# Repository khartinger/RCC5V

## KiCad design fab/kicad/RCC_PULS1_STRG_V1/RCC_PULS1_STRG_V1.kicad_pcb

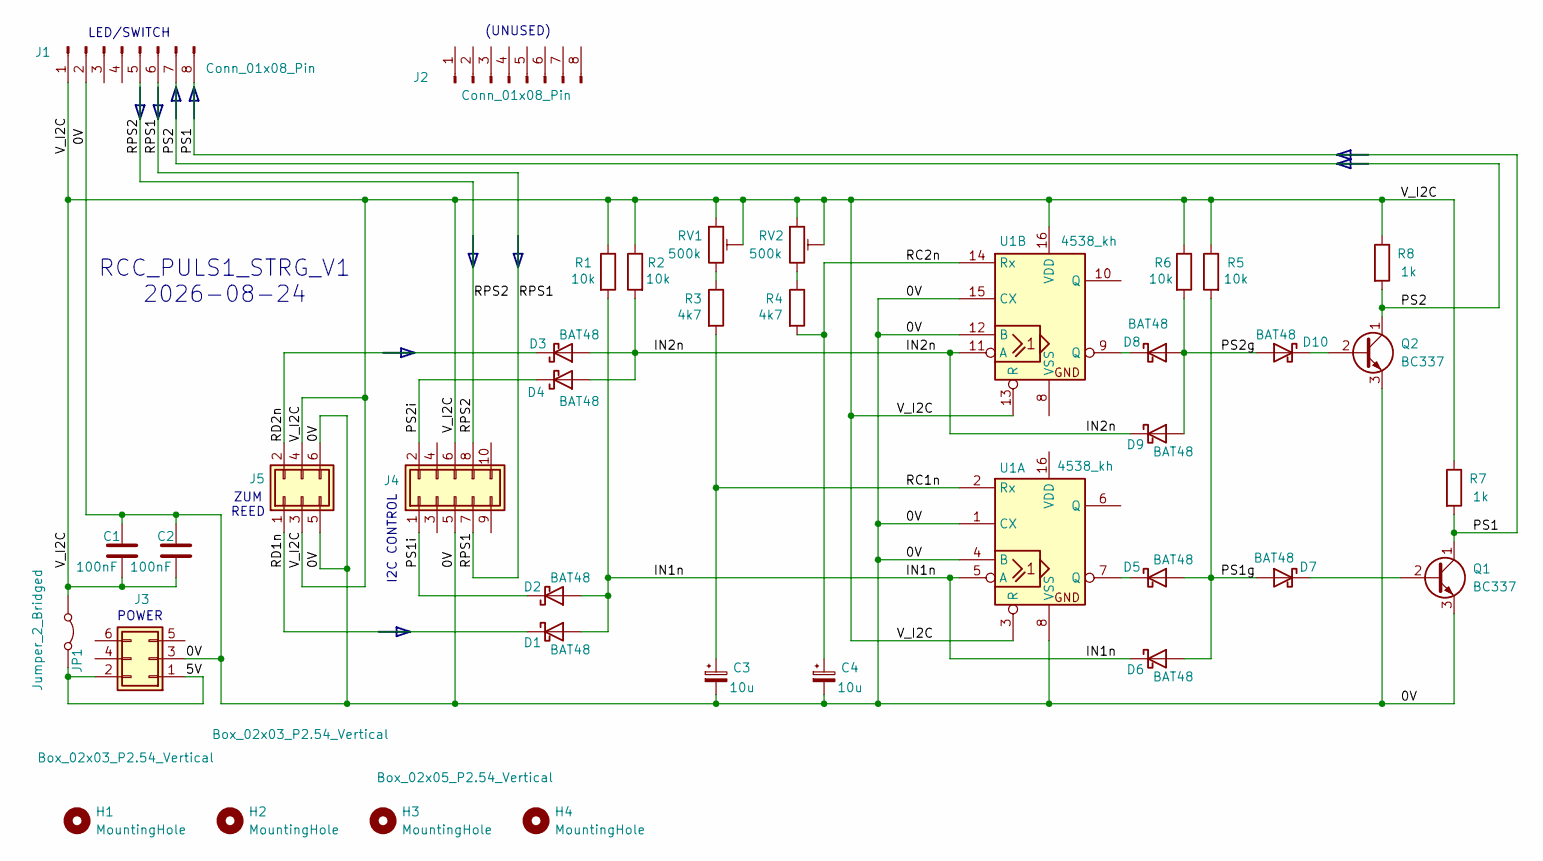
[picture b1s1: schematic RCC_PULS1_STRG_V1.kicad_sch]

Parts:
C1, C2: 100nF; C_Rect_L7.0mm_W2.0mm_P5.00mm_kh
C3, C4: 10u; ELKO_L4.32mm_D3.81mm_P2.54mm_kh
D1, D2, D3: BAT48; D_DO-35_P2.0mm_Vertical_AnodeUp_kh
D4, D5, D6, D7, D8, D9, D10: BAT48; D_DO-35_SOD27_P2.54mm_Vertical_AnodeUp_kh
H1, H2, H3, H4: MountingHole; MountingHole_2.2mm_M2_Pad_TopBottom_kh
J1, J2: Conn_01x08_Pin; PinSocket_1x08_P2.54mm_Vertical_kh
J3, J5: Box_02x03_P2.54_Vertical; Box_02x03_P2.54mm_Vertical_kh
J4: Box_02x05_P2.54_Vertical; Box_02x05_P2.54mm_Vertical_kh
JP1: Jumper_2_Bridged; SolderJumper-2_P1.3mm_Bridged_Pad1.0x1.5mm
Q1, Q2: BC337; TO-92_Inline_Wide_custom
R1, R5: 10k; R_Axial_DIN0204_L3.6mm_D1.6mm_P2.54mm_Vertical
R2, R6: 10k; R_Axial_DIN0204_L3.6mm_D1.6mm_P2.54mm_Vertical_kh
R3: 4k7; R_Axial_DIN0204_L3.6mm_D1.6mm_P2.54mm_Vertical
R4: 4k7; R_Axial_DIN0204_L3.6mm_D1.6mm_P3.81mm_Vertical_kh
R7, R8: 1k; R_Axial_DIN0204_L3.6mm_D1.6mm_P2.54mm_Vertical_kh
RV1, RV2: 500k; Trim_RM-063_Horizontal_kh
U1: 4538_kh; DIP-16_W7.62mm_kh

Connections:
/0V: C1.1, C2.1, C3.2, C4.2, J1.2, J3.3, J4.5, J5.5, J5.6, Q1.3 (E), Q2.3 (E), U1.1 (CX), U1.4 (B), U1.8 (VSS), U1.12 (B), U1.15 (CX)
/5V: J3.1, J3.2, JP1.2 (B)
/IN1n: D1.2 (A), D2.2 (A), D6.1 (K), R1.2, U1.5 (A)
/IN2n: D3.2 (A), D4.2 (A), D9.1 (K), R2.2, U1.11 (A)
/PS1: J1.8, Q1.1 (C), R7.2
/PS1g: D5.2 (A), D6.2 (A), D7.2 (A), R5.2
/PS1i: D2.1 (K), J4.1
/PS2: J1.7, Q2.1 (C), R8.2
/PS2g: D8.2 (A), D9.2 (A), D10.2 (A), R6.2
/PS2i: D4.1 (K), J4.2
/RC1n: C3.1, R3.2, U1.2 (Rx)
/RC2n: C4.1, R4.2, U1.14 (Rx)
/RD1n: D1.1 (K), J5.1
/RD2n: D3.1 (K), J5.2
/RPS1: J1.6, J4.7
/RPS2: J1.5, J4.8
/V_I2C: C1.2, C2.2, J1.1, J4.6, J5.3, J5.4, JP1.1 (A), R1.1, R2.1, R5.1, R6.1, R7.1, R8.1, RV1.1, RV1.2, RV2.1, RV2.2, U1.3 (R), U1.13 (R), U1.16 (VDD)
unnamed: D5.1 (K), U1.7 (Q)
unnamed: D7.1 (K), Q1.2 (B)
unnamed: D8.1 (K), U1.9 (Q)
unnamed: D10.1 (K), Q2.2 (B)
unnamed: R3.1, RV1.3
unnamed: R4.1, RV2.3

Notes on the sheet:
ZUM REED
RCC_PULS1_STRG_V1 2026-08-24
I2C CONTROL
POWER
(UNUSED)
LED/SWITCH

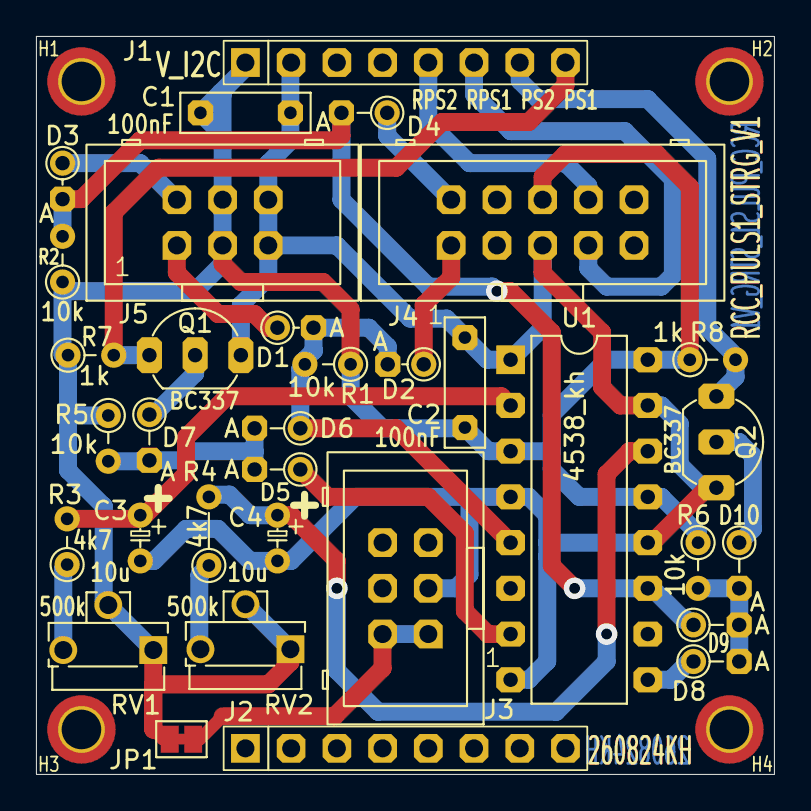
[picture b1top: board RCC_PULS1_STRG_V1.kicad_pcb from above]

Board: 2 copper layers, 41.0 x 41.0 mm, 37 parts (0 on the bottom side), 23 nets.

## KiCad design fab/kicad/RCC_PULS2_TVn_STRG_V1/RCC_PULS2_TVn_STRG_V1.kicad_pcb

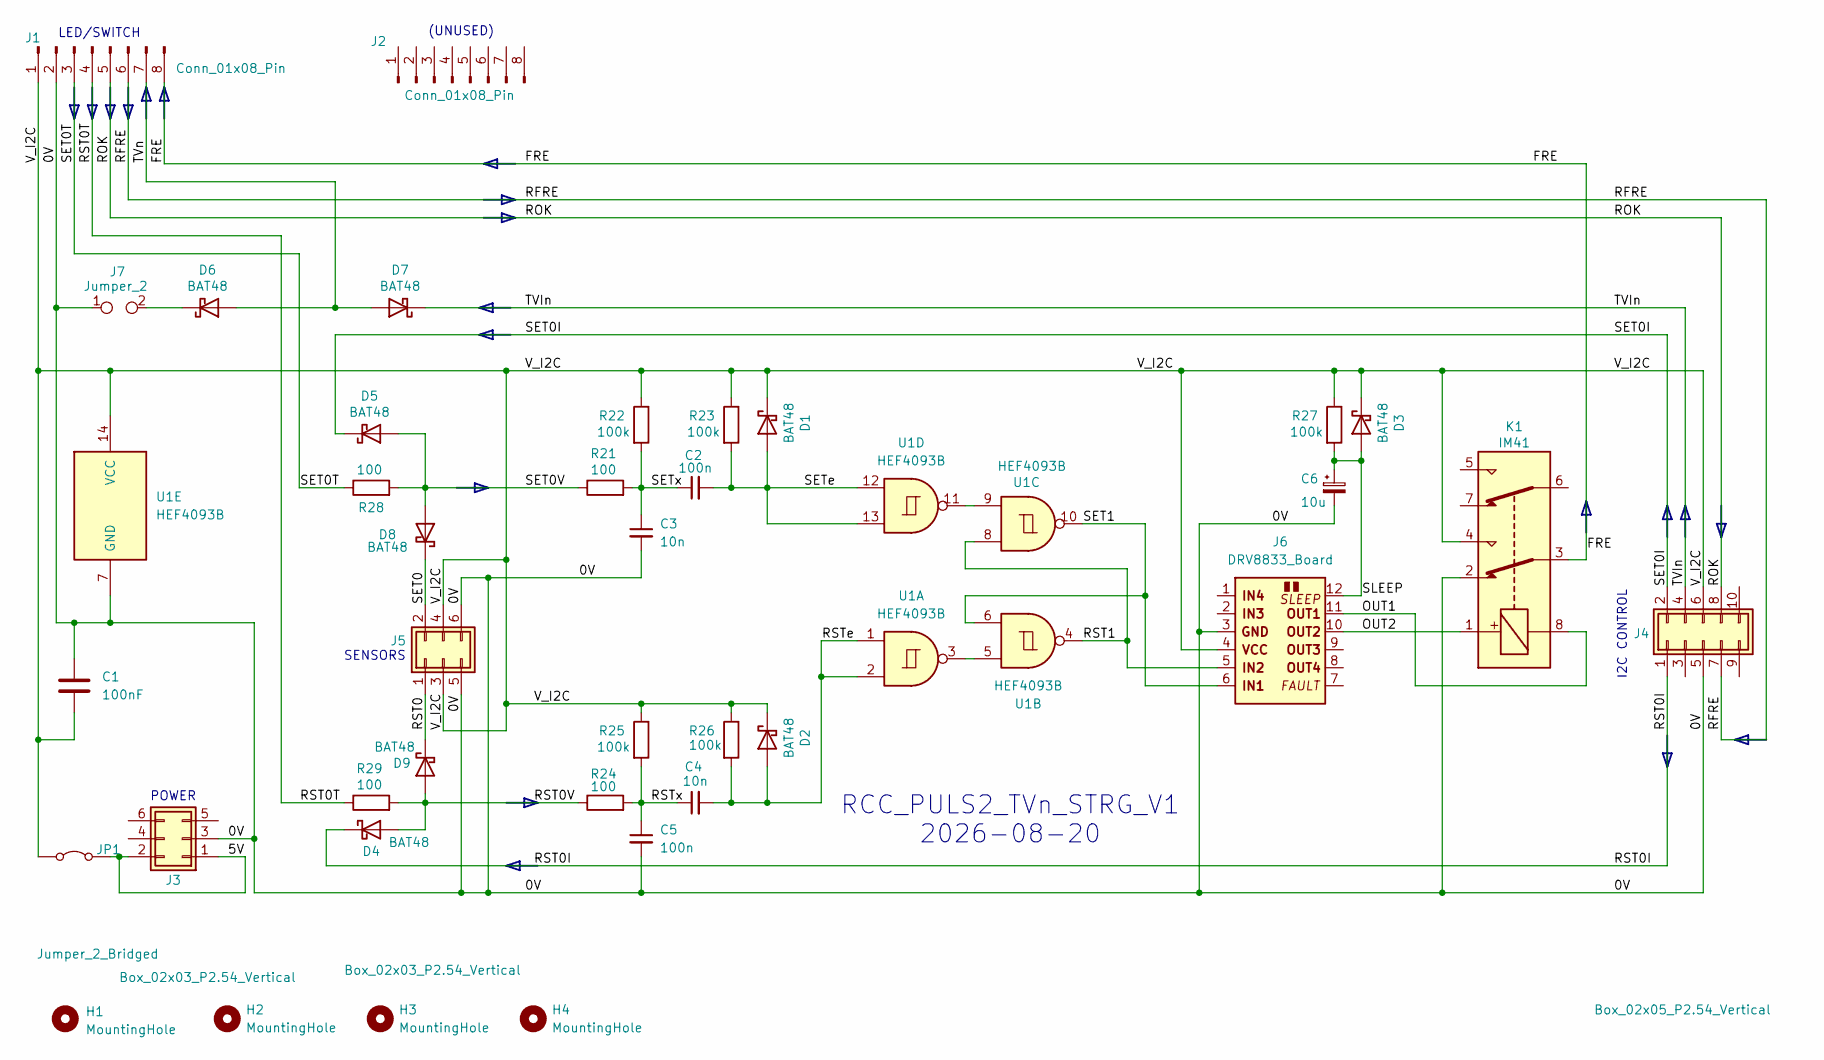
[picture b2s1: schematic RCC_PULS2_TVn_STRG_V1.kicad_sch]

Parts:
C1: 100nF; C_L4mm_D3mm_P2.54mm_kh
C2, C5: 100n; C_L4mm_D3mm_P2.54mm_kh
C3, C4: 10n; C_L4mm_D3mm_P2.54mm_kh
C6: 10u; ELKO_L7.88mm_D4.57mm_P2.54mm_kh
D1, D2, D4: BAT48; D_DO-35_P1.778mm_Vertical_AnodeUp_kh
D3, D6: BAT48; D_DO-35_SOD27_P5.08mm_Horizontal_kh
D5, D8, D9: BAT48; D_DO-35_P2.0mm_Vertical_AnodeUp_kh
D7: BAT48; D_DO-35_SOD27_P2.54mm_Vertical_AnodeUp
H1, H2, H3, H4: MountingHole; MountingHole_2.2mm_M2_Pad_TopBottom_kh
J1, J2: Conn_01x08_Pin; PinSocket_1x08_P2.54mm_Vertical_Back_kh
J3, J5: Box_02x03_P2.54_Vertical; Box_02x03_P2.54mm_Vertical_kh
J4: Box_02x05_P2.54_Vertical; Box_02x05_P2.54mm_Vertical_kh
J6: DRV8833_Board
J7: Jumper_2; PinSocket_1x02_P2.54mm_Vertical_kh
JP1: Jumper_2_Bridged; SolderJumper-2_P1.3mm_Bridged_Pad1.0x1.5mm
K1: IM41; Relay_DPDT_AXICOM_IMSeries_Pitch5.08mm_rect_Pins
R21, R24: 100; R_Axial_P1.778mm_Vertical_kh
R22, R23, R25, R26: 100k; R_Axial_P1.778mm_Vertical_kh
R27: 100k; R_Axial_DIN0204_L3.6mm_D1.6mm_P7.62mm_Horizontal
R28, R29: 100; R_Axial_DIN0204_L3.6mm_D1.6mm_P2.54mm_Vertical_kh
U1: HEF4093B; DIP-14_W7.62mm_Socket_kh

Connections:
/0V: C1.1, C3.2, C5.2, C6.2, J1.2, J3.3, J4.5, J5.5, J5.6, J6.3 (GND), J7.1, K1.2, U1.7 (GND)
/5V: J3.1, J3.2, JP1.2 (B)
/FRE: J1.8, K1.3
/OUT1: J6.11 (OUT1), K1.8
/OUT2: J6.10 (OUT2), K1.1
/RFRE: J1.6, J4.7
/ROK: J1.5, J4.8
/RST0: D9.1 (K), J5.1
/RST0I: D4.1 (K), J4.1
/RST0T: J1.4, R29.1
/RST0V: D4.2 (A), D9.2 (A), R24.1, R29.2
/RST1: J6.5 (IN2), U1.4, U1.8
/RSTe: C4.2, D2.2 (A), R26.2, U1.1, U1.2
/RSTx: C4.1, C5.1, R24.2, R25.2
/SET0: D8.1 (K), J5.2
/SET0I: D5.1 (K), J4.2
/SET0T: J1.3, R28.1
/SET0V: D5.2 (A), D8.2 (A), R21.1, R28.2
/SET1: J6.6 (IN1), U1.6, U1.10
/SETe: C2.2, D1.2 (A), R23.2, U1.12, U1.13
/SETx: C2.1, C3.1, R21.2, R22.2
/SLEEP: C6.1, D3.2 (A), J6.12 (SLEEP), R27.2
/TVIn: D7.1 (K), J4.4
/TVn: D6.2 (A), D7.2 (A), J1.7
/V_I2C: C1.2, D1.1 (K), D2.1 (K), D3.1 (K), J1.1, J4.6, J5.3, J5.4, J6.4 (VCC), JP1.1 (A), K1.4, R22.1, R23.1, R25.1, R26.1, R27.1, U1.14 (VCC)
unnamed: D6.1 (K), J7.2
unnamed: U1.3, U1.5
unnamed: U1.9, U1.11

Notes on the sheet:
SENSORS
I2C CONTROL
POWER
(UNUSED)
LED/SWITCH
RCC_PULS2_TVn_STRG_V1 2026-08-20

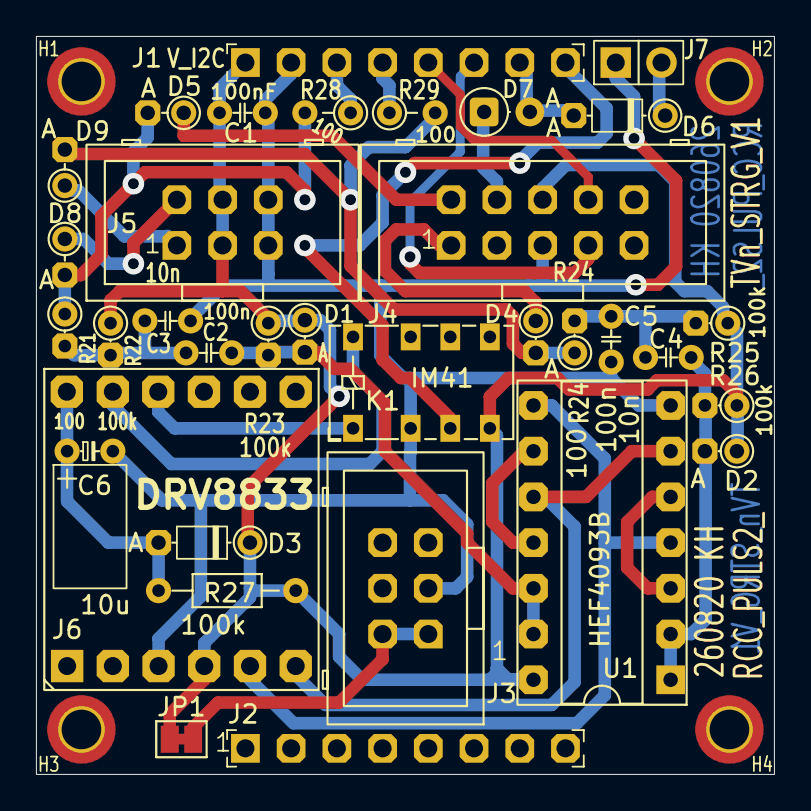
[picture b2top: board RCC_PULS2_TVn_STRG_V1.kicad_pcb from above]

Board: 2 copper layers, 41.0 x 41.0 mm, 38 parts (0 on the bottom side), 28 nets.

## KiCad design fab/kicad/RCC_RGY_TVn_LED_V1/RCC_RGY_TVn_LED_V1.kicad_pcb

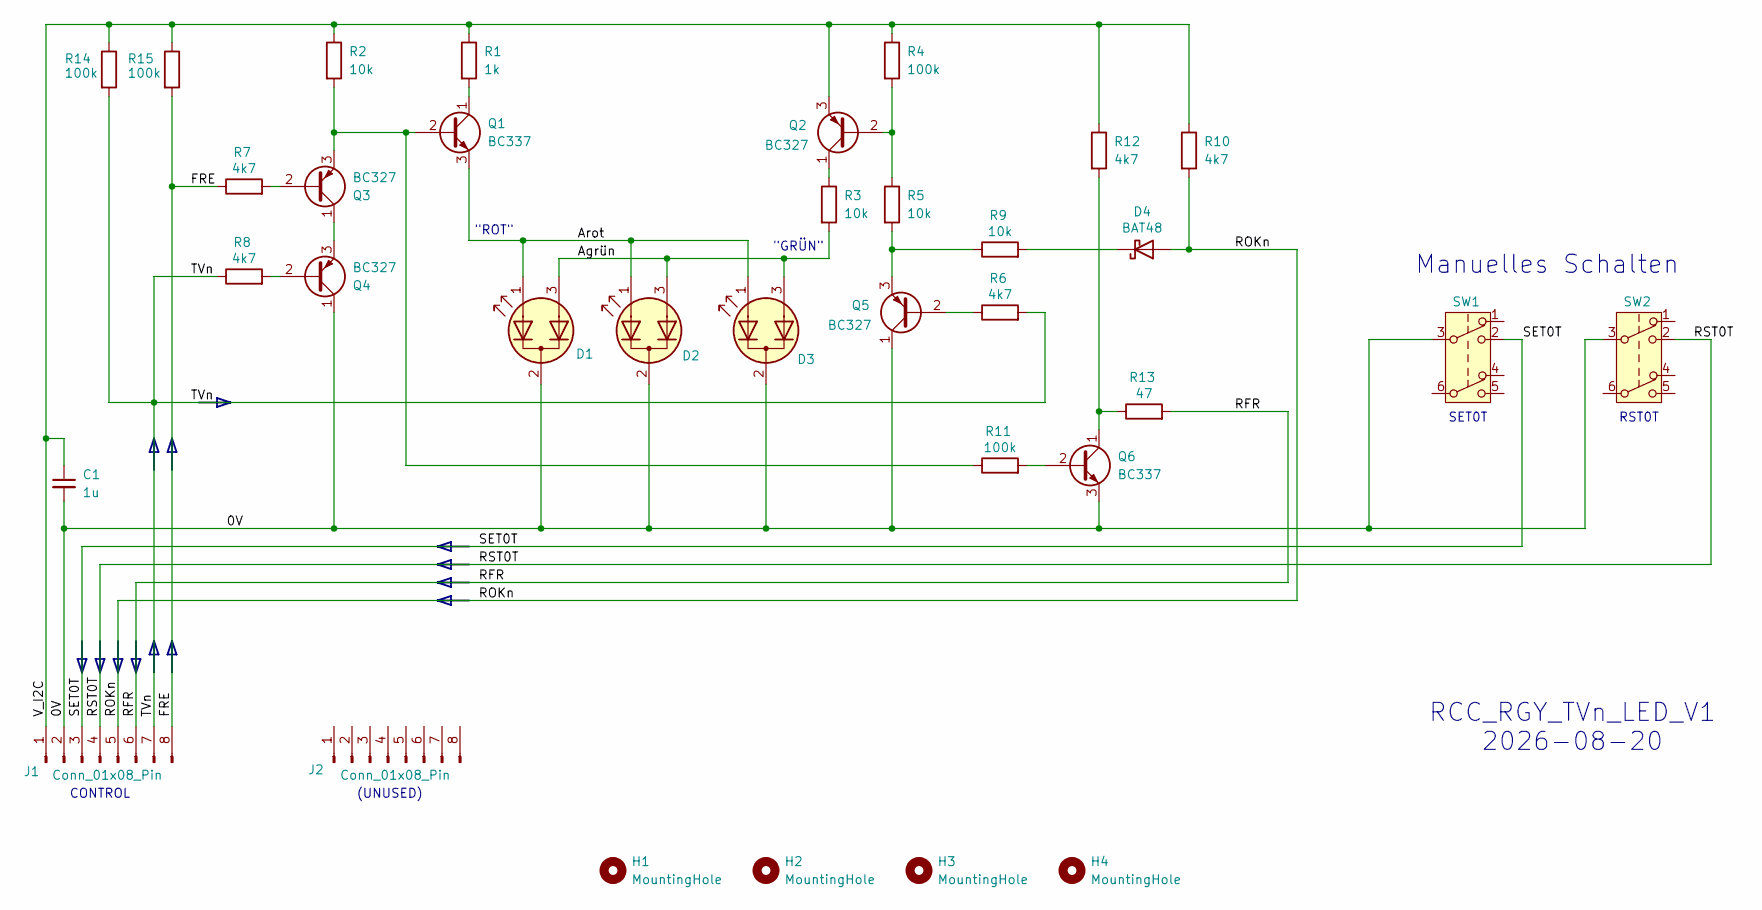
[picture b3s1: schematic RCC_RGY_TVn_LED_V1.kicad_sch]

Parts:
C1: 1u; C_L4mm_D3mm_P2.54mm_kh
D1, D2, D3: LED_Dual_AKA; LED_D5.0mm-3
D4: BAT48; D_DO-35_SOD27_P2.54mm_Vertical_AnodeUp
H1, H2, H3, H4: MountingHole; MountingHole_2.2mm_M2_Pad_TopBottom_kh
J1, J2: Conn_01x08_Pin; PinSocket_1x08_P2.54mm_Vertical_11mm_kh
Q1, Q6: BC337; TO-92_Inline_Wide_custom
Q2, Q3, Q4, Q5: BC327; TO-92_Inline_Wide_custom
R1: 1k; R_Axial_DIN0204_L3.6mm_D1.6mm_P7.62mm_Horizontal
R2, R3, R5: 10k; R_Axial_DIN0204_L3.6mm_D1.6mm_P2.54mm_Vertical
R4, R14, R15: 100k; R_Axial_DIN0204_L3.6mm_D1.6mm_P2.54mm_Vertical
R6, R8: 4k7; R_Axial_DIN0204_L3.6mm_D1.6mm_P2.54mm_Vertical_kh
R7: 4k7; R_Axial_DIN0204_L3.6mm_D1.6mm_P3.81mm_Vertical_kh
R9: 10k; R_Axial_DIN0204_L3.6mm_D1.6mm_P2.54mm_Vertical_kh
R10, R12: 4k7; R_Axial_DIN0204_L3.6mm_D1.6mm_P2.54mm_Vertical
R11: 100k; R_Axial_DIN0204_L3.6mm_D1.6mm_P7.62mm_Horizontal
R13: 47; R_Axial_DIN0204_L3.6mm_D1.6mm_P7.62mm_Horizontal
SW1, SW2: SW_Push_DPDT_8x8

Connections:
/0V: C1.2, D1.2 (K), D2.2 (K), D3.2 (K), J1.2, Q4.1 (C), Q5.1 (C), Q6.3 (E), SW1.3 (C), SW2.3 (C)
/Agrün: D1.3 (A2), D2.3 (A2), D3.3 (A2), R3.2
/Arot: D1.1 (A1), D2.1 (A1), D3.1 (A1), Q1.3 (E)
/FRE: J1.8, R7.1, R15.2
/RFR: J1.6, R13.2
/ROKn: D4.2 (A), J1.5, R10.2
/RST0T: J1.4, SW2.2 (B)
/SET0T: J1.3, SW1.2 (B)
/TVn: J1.7, R6.2, R8.1, R14.2
/V_I2C: C1.1, J1.1, Q2.3 (E), R1.1, R2.1, R4.1, R10.1, R12.1, R14.1, R15.1
unnamed: D4.1 (K), R9.2
unnamed: Q1.2 (B), Q3.3 (E), R2.2, R11.1
unnamed: Q1.1 (C), R1.2
unnamed: Q2.2 (B), R4.2, R5.1
unnamed: Q2.1 (C), R3.1
unnamed: Q3.2 (B), R7.2
unnamed: Q3.1 (C), Q4.3 (E)
unnamed: Q4.2 (B), R8.2
unnamed: Q5.2 (B), R6.1
unnamed: Q5.3 (E), R5.2, R9.1
unnamed: Q6.2 (B), R11.2
unnamed: Q6.1 (C), R12.2, R13.1

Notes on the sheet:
(UNUSED)
SET0T
Manuelles Schalten
"GRÜN"
RCC_RGY_TVn_LED_V1 2026-08-20
CONTROL
"ROT"
RST0T

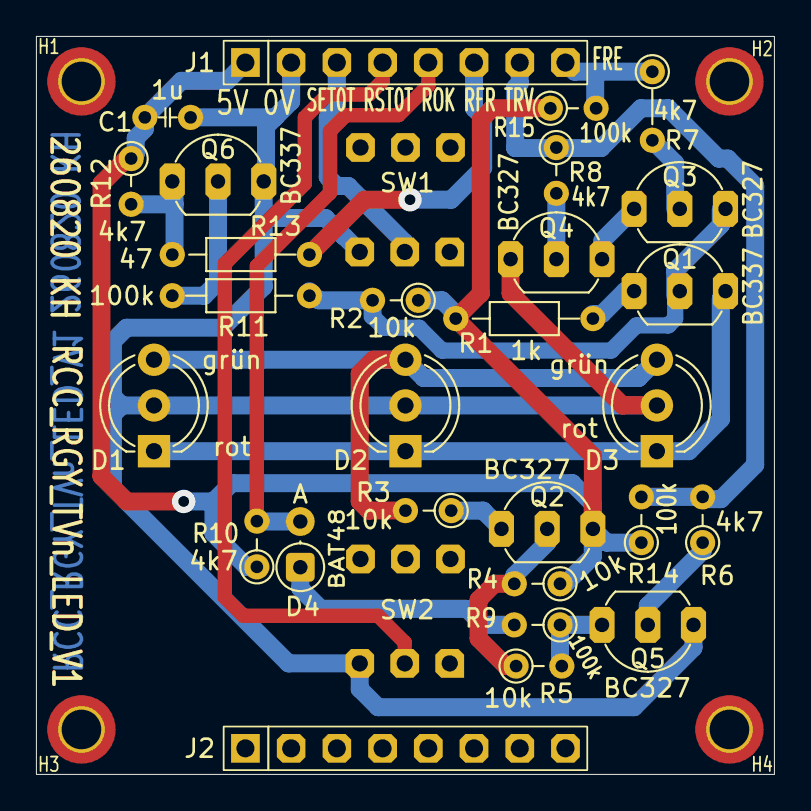
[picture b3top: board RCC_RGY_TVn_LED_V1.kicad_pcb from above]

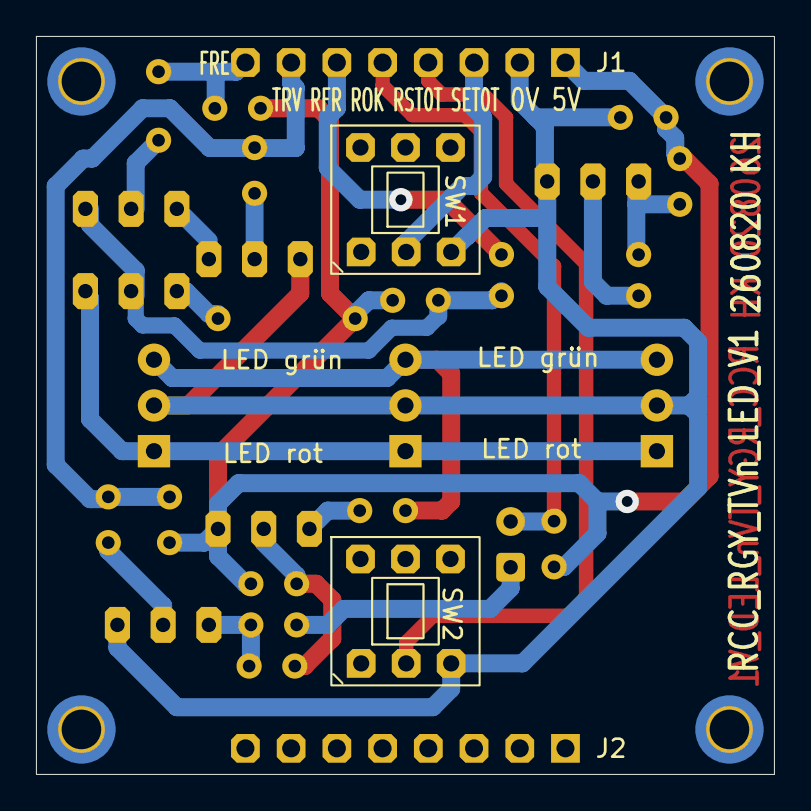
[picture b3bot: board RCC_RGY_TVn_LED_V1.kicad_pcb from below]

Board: 2 copper layers, 41.0 x 41.0 mm, 34 parts (2 on the bottom side), 22 nets.

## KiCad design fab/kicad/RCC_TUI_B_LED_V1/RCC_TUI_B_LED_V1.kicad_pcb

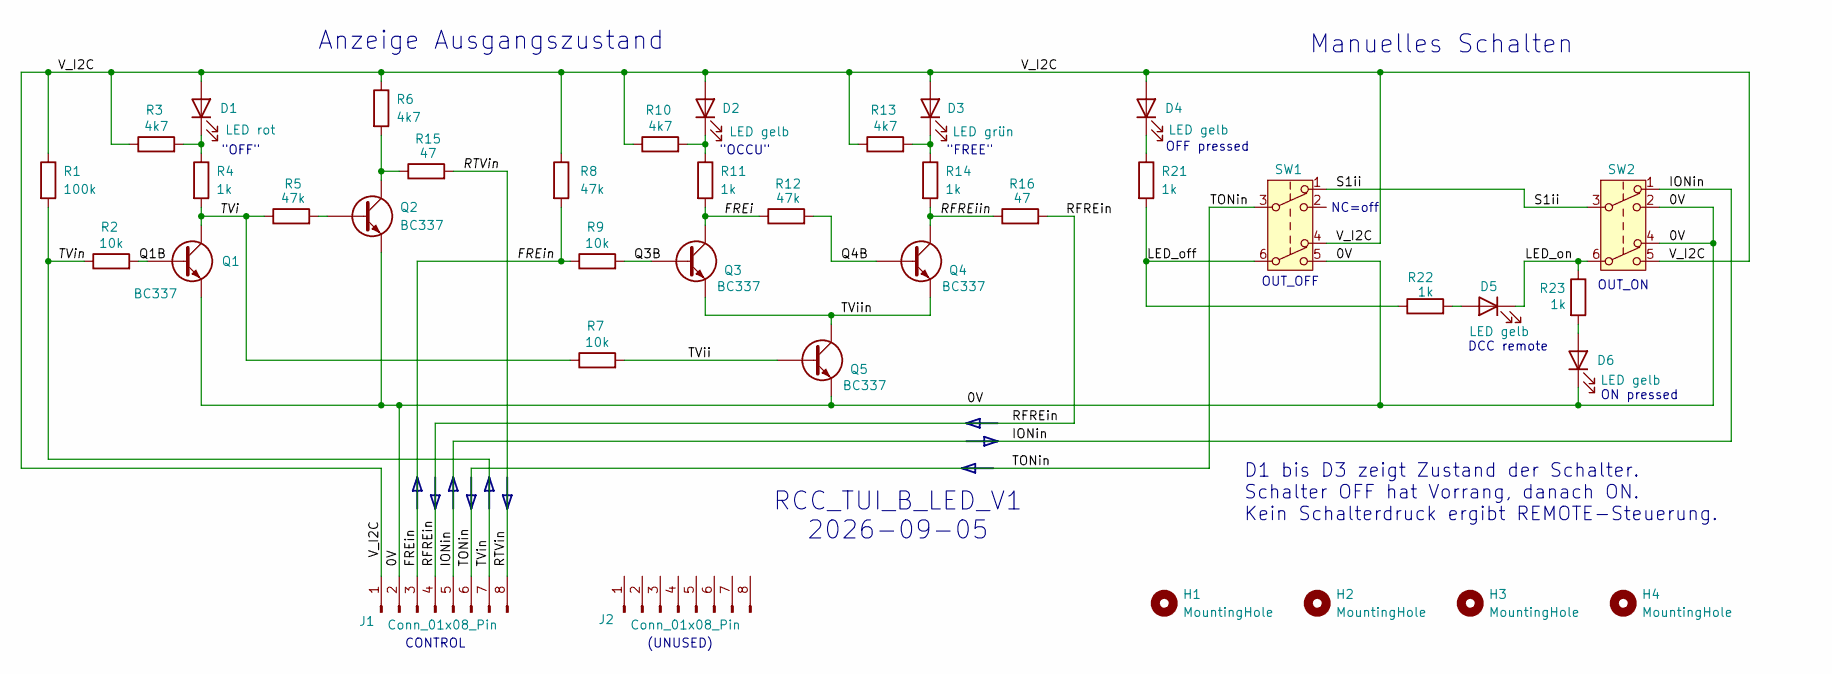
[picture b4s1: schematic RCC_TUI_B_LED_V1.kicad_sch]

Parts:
D1: LED rot; LED_D3.0mm_kh
D2, D4, D5, D6: LED gelb; LED_D3.0mm_kh
D3: LED grün; LED_D3.0mm_kh
H1, H2, H3, H4: MountingHole; MountingHole_2.2mm_M2_Pad_TopBottom_kh
J1, J2: Conn_01x08_Pin; PinSocket_1x08_P2.54mm_Vertical_11mm_kh
Q1, Q2, Q3, Q4, Q5: BC337; TO-92_Inline_Wide_custom
R1: 100k; R_Axial_DIN0204_L3.6mm_D1.6mm_P2.54mm_Vertical
R2, R7, R9: 10k; R_Axial_DIN0204_L3.6mm_D1.6mm_P2.54mm_Vertical_kh
R3, R10, R13: 4k7; R_Axial_DIN0204_L3.6mm_D1.6mm_P2.54mm_Vertical_kh
R4, R21, R22, R23: 1k; R_Axial_DIN0204_L3.6mm_D1.6mm_P2.54mm_Vertical_kh
R5, R8, R12: 47k; R_Axial_DIN0204_L3.6mm_D1.6mm_P2.54mm_Vertical_kh
R6: 4k7; R_Axial_DIN0204_L3.6mm_D1.6mm_P2.54mm_Vertical
R11, R14: 1k; R_Axial_DIN0204_L3.6mm_D1.6mm_P2.54mm_Vertical
R15: 47; R_Axial_DIN0204_L3.6mm_D1.6mm_P3.81mm_Vertical_kh
R16: 47; R_Axial_DIN0207_L6.3mm_D2.5mm_P12.7mm_Horizontal_kh
SW1, SW2: SW_Push_DPDT_8x8

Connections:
/0V: D6.1 (K), J1.2, Q1.3 (E), Q2.3 (E), Q5.3 (E), SW1.5 (B), SW2.2 (B), SW2.4 (A)
/FREi: Q3.1 (C), R11.2, R12.1
/FREin: J1.3, R8.2, R9.1
/IONin: J1.5, SW2.1 (A)
/LED_off: R21.2, R22.1, SW1.6 (C)
/LED_on: D5.1 (K), R23.1, SW2.6 (C)
/Q1B: Q1.2 (B), R2.2
/Q3B: Q3.2 (B), R9.2
/Q4B: Q4.2 (B), R12.2
/RFREiin: Q4.1 (C), R14.2, R16.1
/RFREin: J1.4, R16.2
/RTVin: J1.8, R15.2
/S1ii: SW1.1 (A), SW2.3 (C)
/TONin: J1.6, SW1.3 (C)
/TVi: Q1.1 (C), R4.2, R5.1, R7.1
/TVii: Q5.2 (B), R7.2
/TViin: Q3.3 (E), Q4.3 (E), Q5.1 (C)
/TVin: J1.7, R1.2, R2.1
/V_I2C: D1.2 (A), D2.2 (A), D3.2 (A), D4.2 (A), J1.1, R1.1, R3.1, R6.1, R8.1, R10.1, R13.1, SW1.4 (A), SW2.5 (B)
unnamed: D1.1 (K), R3.2, R4.1
unnamed: D2.1 (K), R10.2, R11.1
unnamed: D3.1 (K), R13.2, R14.1
unnamed: D4.1 (K), R21.1
unnamed: D5.2 (A), R22.2
unnamed: D6.2 (A), R23.2
unnamed: Q2.2 (B), R5.2
unnamed: Q2.1 (C), R6.2, R15.1

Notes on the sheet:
ON pressed
(UNUSED)
OUT_OFF
"OCCU"
D1 bis D3 zeigt Zustand der Schalter. Schalter OFF hat Vorrang, danach ON. Kein Schalterdruck ergibt REMOTE-Steuerung.
Manuelles Schalten
"OFF"
CONTROL
OUT_ON
OFF pressed
Anzeige Ausgangszustand
"FREE"
RCC_TUI_B_LED_V1 2026-09-05
DCC remote
NC=off

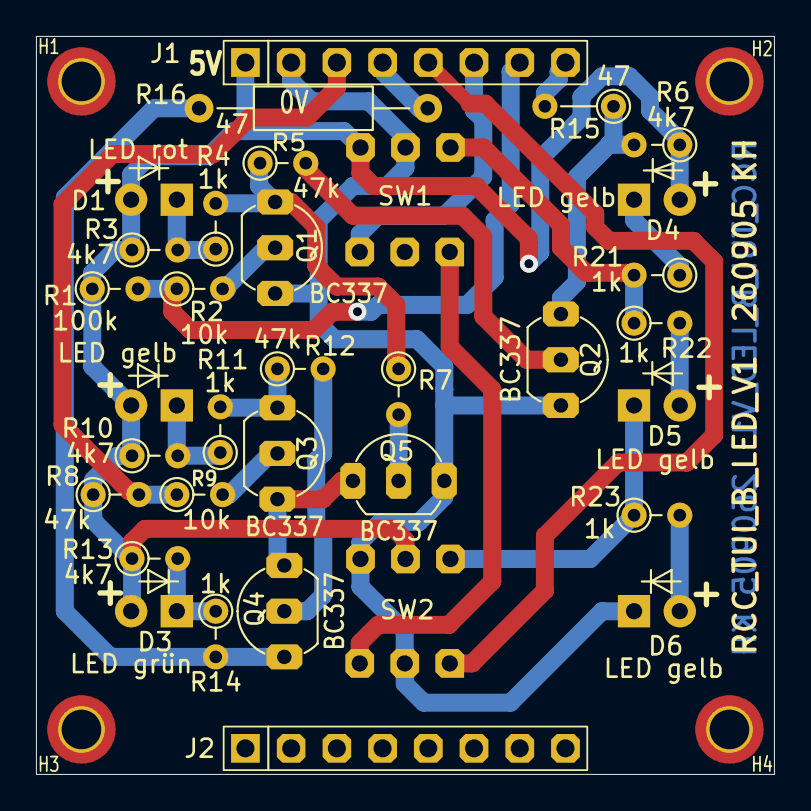
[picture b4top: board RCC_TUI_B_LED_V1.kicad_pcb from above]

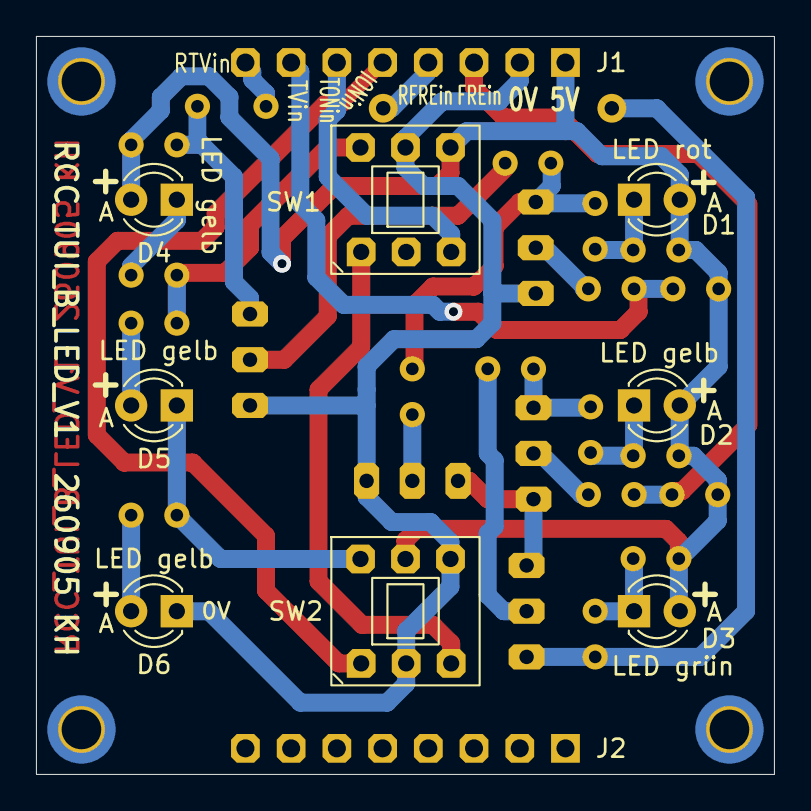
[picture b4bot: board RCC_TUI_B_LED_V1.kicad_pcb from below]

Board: 2 copper layers, 41.0 x 41.0 mm, 38 parts (8 on the bottom side), 27 nets.

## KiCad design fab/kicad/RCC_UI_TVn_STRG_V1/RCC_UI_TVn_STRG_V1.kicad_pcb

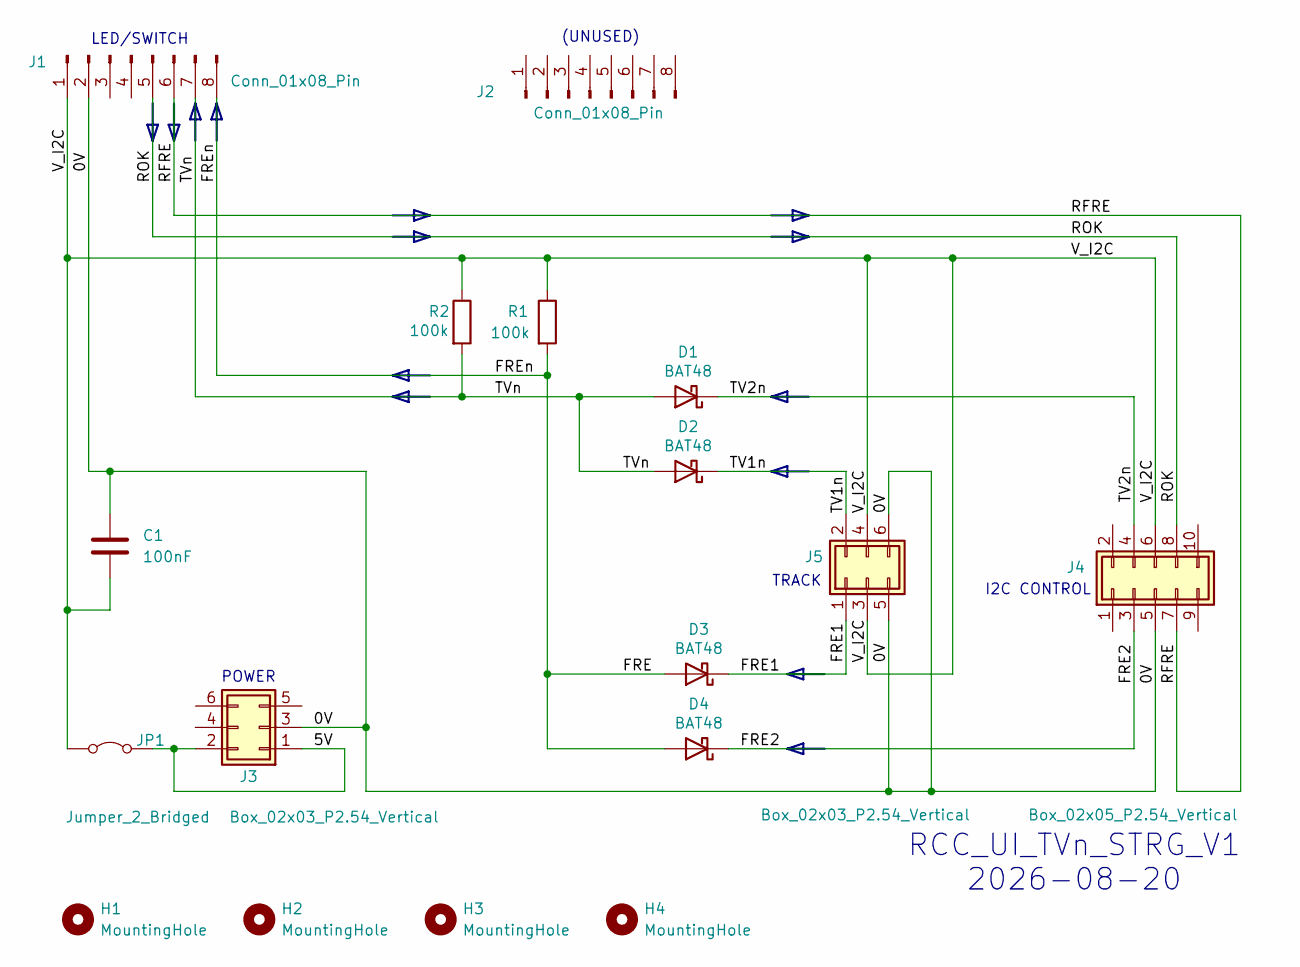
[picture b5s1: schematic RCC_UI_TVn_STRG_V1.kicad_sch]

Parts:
C1: 100nF; C_Rect_L7.0mm_W2.0mm_P5.00mm_kh
D1, D2: BAT48; D_DO-35_SOD27_P2.54mm_Vertical_AnodeUp
D3, D4: BAT48; D_DO-35_SOD27_P5.08mm_Vertical_AnodeUp
H1, H2, H3, H4: MountingHole; MountingHole_2.2mm_M2_Pad_TopBottom_kh
J1, J2: Conn_01x08_Pin; PinSocket_1x08_P2.54mm_Vertical_kh
J3, J5: Box_02x03_P2.54_Vertical; Box_02x03_P2.54mm_Vertical_kh
J4: Box_02x05_P2.54_Vertical; Box_02x05_P2.54mm_Vertical_kh
JP1: Jumper_2_Bridged; SolderJumper-2_P1.3mm_Bridged_Pad1.0x1.5mm
R1: 100k; R_Axial_DIN0204_L3.6mm_D1.6mm_P2.54mm_Vertical
R2: 100k; R_Axial_DIN0204_L3.6mm_D1.6mm_P5.08mm_Vertical

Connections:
/0V: C1.1, J1.2, J3.3, J4.5, J5.5, J5.6
/5V: J3.1, J3.2, JP1.2 (B)
/FRE: D3.2 (A), D4.2 (A), J1.8, R1.2
/FRE1: D3.1 (K), J5.1
/FRE2: D4.1 (K), J4.3
/RFRE: J1.6, J4.7
/ROK: J1.5, J4.8
/TV1n: D2.1 (K), J5.2
/TV2n: D1.1 (K), J4.4
/TVn: D1.2 (A), D2.2 (A), J1.7, R2.2
/V_I2C: C1.2, J1.1, J4.6, J5.3, J5.4, JP1.1 (A), R1.1, R2.1

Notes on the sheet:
TRACK
RCC_UI_TVn_STRG_V1 2026-08-20
I2C CONTROL
POWER
(UNUSED)
LED/SWITCH

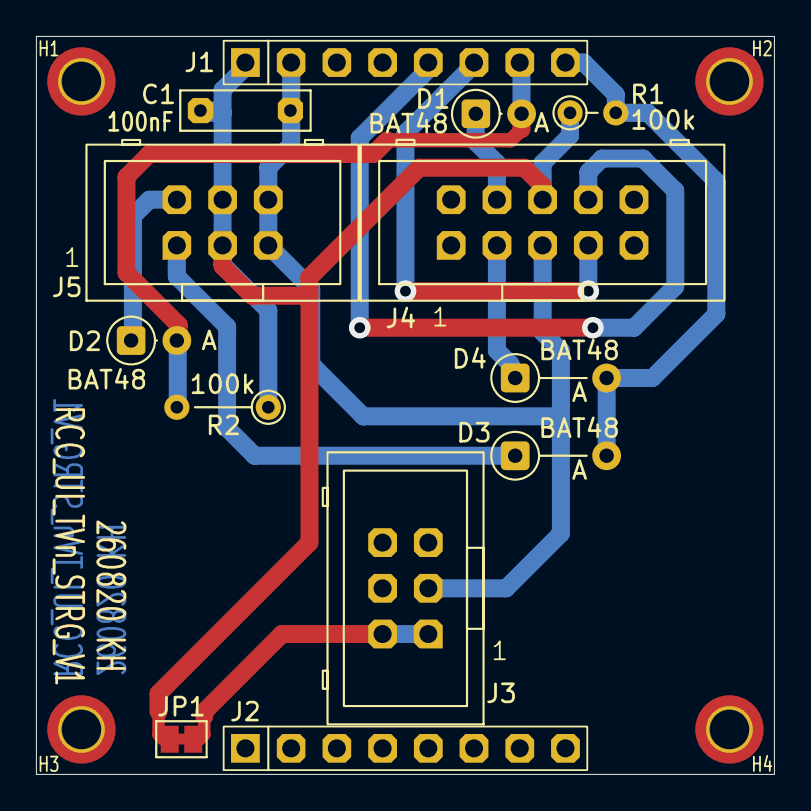
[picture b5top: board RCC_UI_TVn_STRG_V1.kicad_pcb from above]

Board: 2 copper layers, 41.0 x 41.0 mm, 17 parts (0 on the bottom side), 11 nets.

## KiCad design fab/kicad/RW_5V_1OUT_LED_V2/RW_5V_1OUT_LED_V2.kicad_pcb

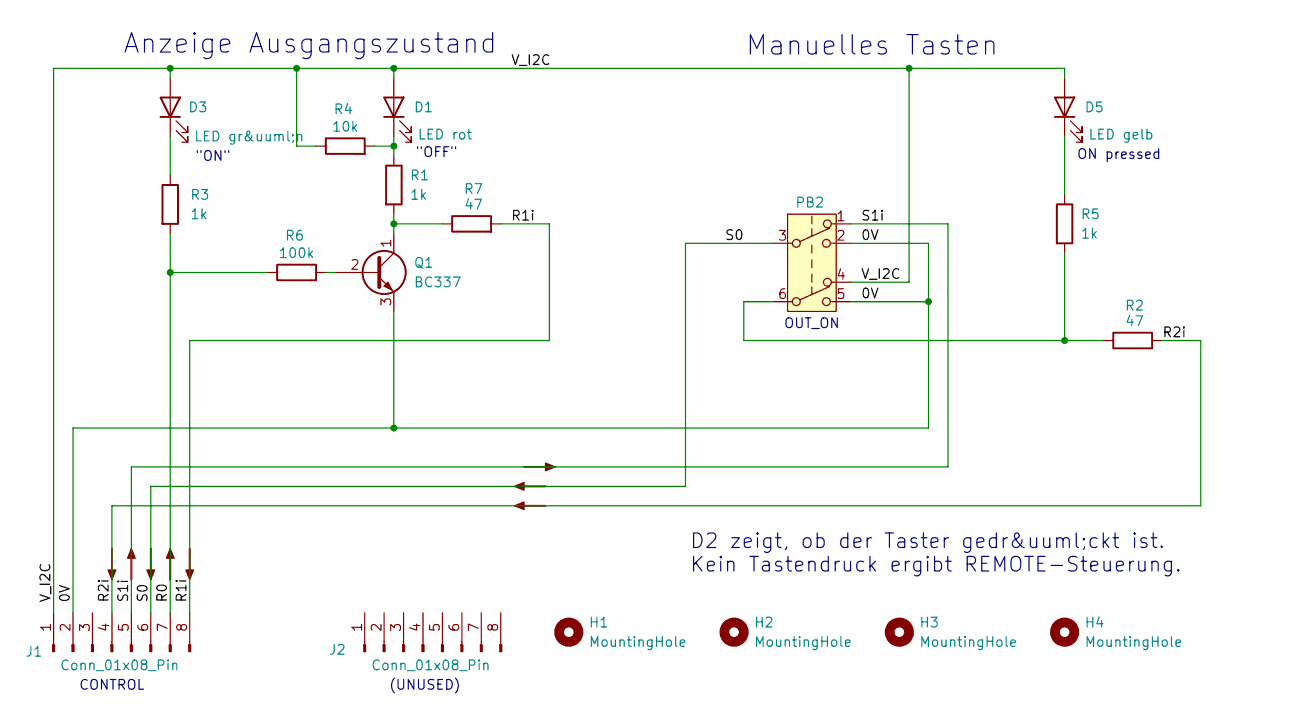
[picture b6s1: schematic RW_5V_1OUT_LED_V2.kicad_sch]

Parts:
D1: LED rot; LED_D3.0mm
D3: LED gr&uuml;n; LED_D3.0mm
D5: LED gelb; LED_D3.0mm
H1, H2, H3, H4: MountingHole; MountingHole_2.2mm_M2_Pad_TopBottom_kh
J1, J2: Conn_01x08_Pin; PinSocket_1x08_P2.54mm_Vertical_11mm_kh
PB2: SW_Push_DPDT_8x8
Q1: BC337; TO-92_Inline_Wide_custom
R1, R3: 1k; R_Axial_DIN0204_L3.6mm_D1.6mm_P2.54mm_Vertical
R2, R7: 47; R_Axial_DIN0204_L3.6mm_D1.6mm_P2.54mm_Vertical
R4: 10k; R_Axial_DIN0204_L3.6mm_D1.6mm_P2.54mm_Vertical_kh
R5: 1k; R_Axial_DIN0204_L3.6mm_D1.6mm_P10,16mm_Horizontal
R6: 100k; R_Axial_DIN0204_L3.6mm_D1.6mm_P2.54mm_Vertical_kh

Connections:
/0V: J1.2, PB2.2 (B), PB2.5 (B), Q1.3 (E)
/R0: J1.7, R3.2, R6.1
/R1i: J1.8, R7.2
/R2i: J1.4, R2.2
/S0: J1.6, PB2.3 (C)
/S1i: J1.5, PB2.1 (A)
/V_I2C: D1.2 (A), D3.2 (A), D5.2 (A), J1.1, PB2.4 (A), R4.1
unnamed: D1.1 (K), R1.1, R4.2
unnamed: D3.1 (K), R3.1
unnamed: D5.1 (K), R5.1
unnamed: PB2.6 (C), R2.1, R5.2
unnamed: Q1.2 (B), R6.2
unnamed: Q1.1 (C), R1.2, R7.1

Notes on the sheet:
(UNUSED)
OUT_ON
D2 zeigt, ob der Taster gedr&uuml;ckt ist. Kein Tastendruck ergibt REMOTE-Steuerung.
Manuelles Tasten
"OFF"
ON pressed
CONTROL
Anzeige Ausgangszustand
"ON"

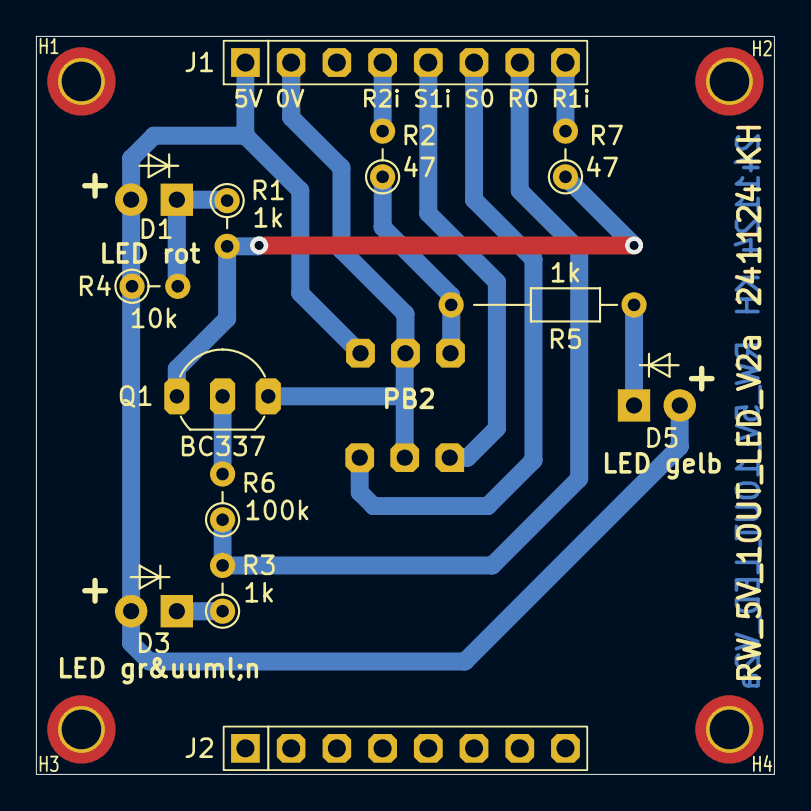
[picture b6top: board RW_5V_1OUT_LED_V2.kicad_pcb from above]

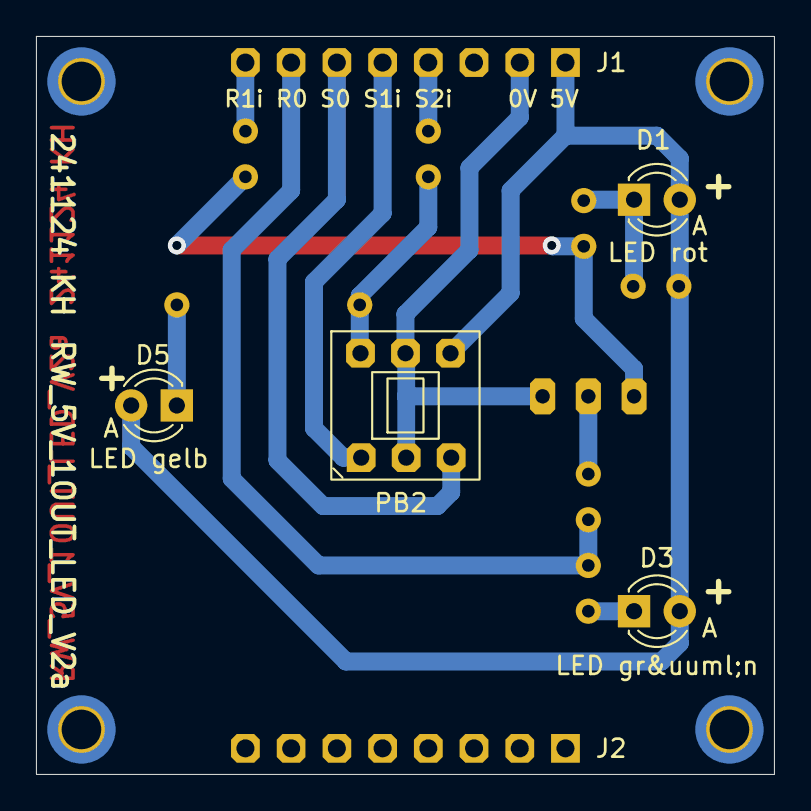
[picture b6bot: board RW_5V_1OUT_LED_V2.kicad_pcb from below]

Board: 2 copper layers, 41.0 x 41.0 mm, 18 parts (4 on the bottom side), 13 nets.

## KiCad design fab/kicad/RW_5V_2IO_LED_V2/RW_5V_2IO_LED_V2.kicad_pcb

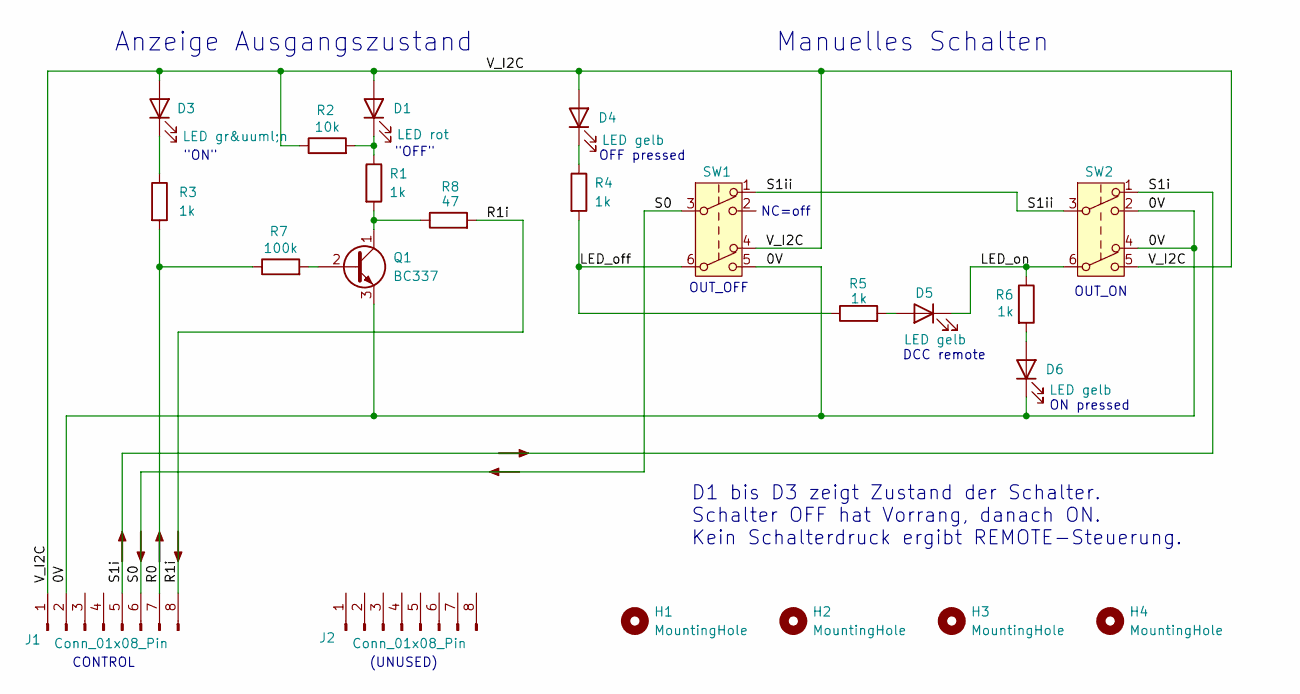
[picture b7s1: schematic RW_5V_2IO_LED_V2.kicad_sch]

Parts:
D1: LED rot; LED_D3.0mm
D3: LED gr&uuml;n; LED_D3.0mm
D4, D5, D6: LED gelb; LED_D3.0mm
H1, H2, H3, H4: MountingHole; MountingHole_2.2mm_M2_Pad_TopBottom_kh
J1, J2: Conn_01x08_Pin; PinSocket_1x08_P2.54mm_Vertical_11mm_kh
Q1: BC337; TO-92_Inline_Wide_custom
R1, R3, R4, R5, R6: 1k; R_Axial_DIN0204_L3.6mm_D1.6mm_P2.54mm_Vertical
R2: 10k; R_Axial_DIN0204_L3.6mm_D1.6mm_P2.54mm_Vertical_kh
R7: 100k; R_Axial_DIN0204_L3.6mm_D1.6mm_P3.81mm_Vertical_kh
R8: 47; R_Axial_DIN0204_L3.6mm_D1.6mm_P10,16mm_Horizontal
SW1, SW2: SW_Push_DPDT_8x8

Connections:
/0V: D6.1 (K), J1.2, Q1.3 (E), SW1.5 (B), SW2.2 (B), SW2.4 (A)
/LED_off: R4.2, R5.1, SW1.6 (C)
/LED_on: D5.1 (K), R6.1, SW2.6 (C)
/R0: J1.7, R3.2, R7.1
/R1i: J1.8, R8.2
/S0: J1.6, SW1.3 (C)
/S1i: J1.5, SW2.1 (A)
/S1ii: SW1.1 (A), SW2.3 (C)
/V_I2C: D1.2 (A), D3.2 (A), D4.2 (A), J1.1, R2.1, SW1.4 (A), SW2.5 (B)
unnamed: D1.1 (K), R1.1, R2.2
unnamed: D3.1 (K), R3.1
unnamed: D4.1 (K), R4.1
unnamed: D5.2 (A), R5.2
unnamed: D6.2 (A), R6.2
unnamed: Q1.2 (B), R7.2
unnamed: Q1.1 (C), R1.2, R8.1

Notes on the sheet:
ON pressed
(UNUSED)
OUT_OFF
D1 bis D3 zeigt Zustand der Schalter. Schalter OFF hat Vorrang, danach ON. Kein Schalterdruck ergibt REMOTE-Steuerung.
Manuelles Schalten
"OFF"
CONTROL
OUT_ON
OFF pressed
Anzeige Ausgangszustand
"ON"
DCC remote
NC=off
